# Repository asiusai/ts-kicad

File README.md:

# ts-kicad

TypeScript schematics, BOMs and KiCad settings. Requires Bun and KiCad 10 with its symbol, footprint and 3D model libraries. JLC imports also need `uv`; fabrication exports need `zip`.

1. Use builtins from `ts-kicad/lib/symbols/*` and `ts-kicad/lib/footprints/*`, or import parts with `ts-kicad jlc C123 C456`. JLC imports go into `lib/<part-number>/`, with unspecified pins made passive. For manually imported assets in `lib/<name>/`, run `ts-kicad convert [name ...]` to generate `symbols.ts` and `footprints.ts` per folder.
2. Define the circuit in `src/index.ts` and default-export a `Project`. Set footprints and manufacturer/part details in `Project.bom`. See [harness-box](examples/harness-box/src/index.ts).
3. Run `ts-kicad sync` to generate the schematic and project settings. Open KiCad, update the PCB from the schematic, then place and route the board there.
4. Run `ts-kicad export` to write BOM, PDF, fabrication files, positions and mechanical models into `outputs/`. ERC/DRC findings and schematic/PCB mismatches are logged without blocking export; JSON check reports are temporary and are not exported.

Generated labels for unnamed nets use component and pin names, such as
`Net-(Q2-G)` or `Net-(R10-Pad2)`. Explicit signal and power names remain unchanged.

Sync verifies the generated schematic through KiCad's native netlist and compares
any existing PCB's saved pad nets and full schematic UUID paths with that netlist.
Board-only footprints do not need schematic links. If these checks pass, native KiCad
schematic parity also checks symbol fields, footprint identities and escaped net
names. It reports mismatches without changing PCB placement or routing.
After an external sync, reload the schematic in KiCad before using Update PCB
from Schematic (F8); an already-open editor may still hold the previous circuit.
Project settings edited in KiCad are preserved unless explicitly set in the
TypeScript project.

Fabrication export includes KiCad's via filling/capping/plugging/covering Gerber
artwork alongside the Excellon drills. Specify the fill material in fabrication
notes and select the corresponding factory process when ordering.
Project-local fabrication notes are not copied into the outputs or Gerber ZIP.

BOM rows with an assigned JLC/LCSC part number are grouped by that number and
population status. Different schematic value labels or footprint aliases for
the same purchased part are listed together in one row. Native DNP parts are
excluded from BOM.csv and pos.csv. Their schematic and PCB flags remain intact.
Paste exports omit DNP and BOM-excluded parts. Native copper, mask, and footprint geometry remain unchanged.
Off-board variants remain separate. Parts without a supplier number group by
their full exported fields.

The JLC `pos.csv` uses millimetres and component-side rotation angles: top
angles stay unchanged; bottom angles become `180 - KiCad angle`, normalized to
0 through 360 degrees (exclusive). Coordinates are not mirrored for the bottom.
This follows [Fabrication Toolkit's conversion](https://github.com/bennymeg/Fabrication-Toolkit/blob/master/plugins/process.py).
Individual footprint zero angles can still differ from JLC's component library.
Check pin 1, polarity and connector direction in the assembly preview; matching
the native KiCad angles alone does not verify assembly orientation.

Sync keeps KiCad's complete Default netclass, including its schematic wire and
bus widths. Partial PCB netclass settings inherit these defaults. Junction dots
are calculated after power-label wires are added, so branch connections survive
the schematic editor's wire cleanup as well as command-line netlist export.

Components accept a reference first: `r("R27", { value: "100R" })` or
`new R("R27", { value: "100R" })`. Options are optional, so `new PWR_FLAG("#FLG01")`
also works. The object-only form `r({ ref: "R27", value: "100R" })` remains supported.
When both arguments specify a reference, the first argument takes precedence.

Run commands from the project directory. Separate part numbers or folder names with spaces; quote names containing spaces. The two `internal-*` commands regenerate this package's builtins during development.

```text
$ ts-kicad
Usage: ts-kicad <command> [options]

  sync                Sync the TypeScript circuit/settings into KiCad.
  export              Log ERC/DRC findings and export BOM, PDF, fabrication files, positions and mechanical models.
  convert             Generate symbols.ts and footprints.ts for all lib folders or selected folders.
  jlc                 Import JLCPCB parts into lib/PART_NO and convert those folders.
  internal-symbols    Regenerate lib/symbols from installed KiCad libraries (package development).
  internal-footprints Regenerate lib/footprints from installed KiCad libraries (package development).

Use ts-kicad <command> --help for arguments. Paths are relative to the current directory.
```

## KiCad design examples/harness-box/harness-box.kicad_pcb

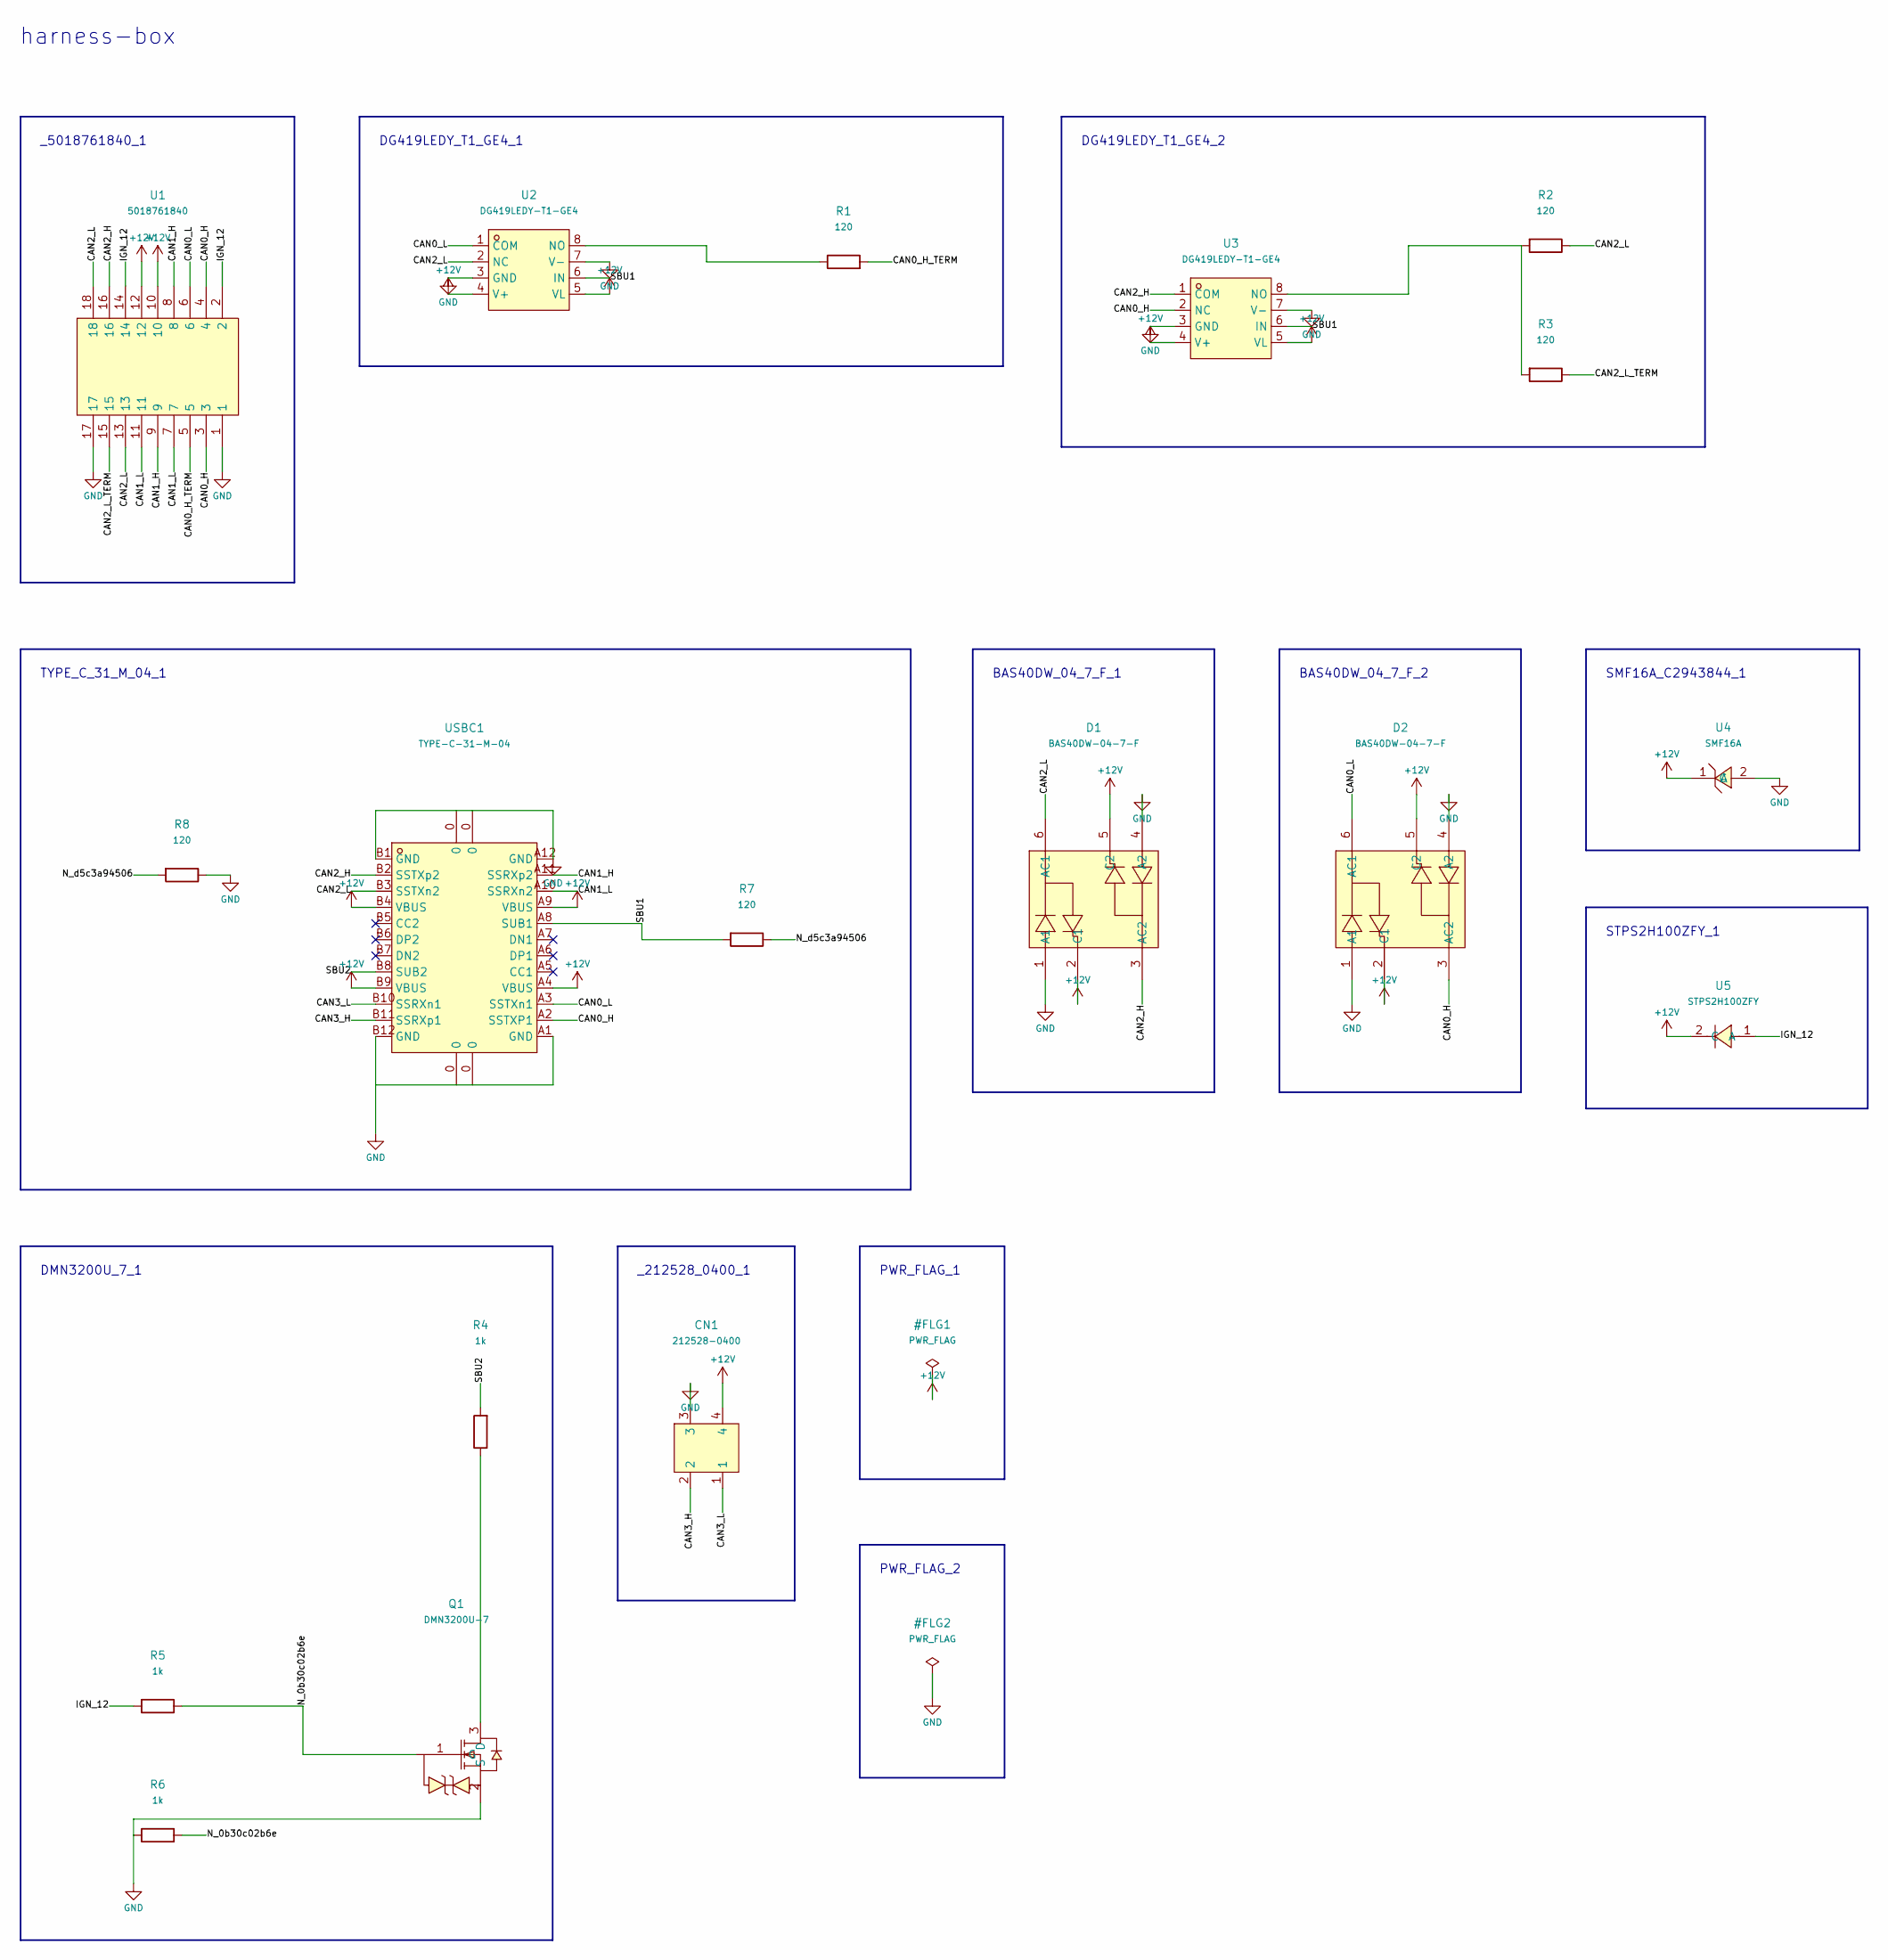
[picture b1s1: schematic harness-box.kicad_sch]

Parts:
CN1: 212528-0400; CONN-TH_4P-P3.00_212528-0400; MFR.Part # 212528-0400; JLCPCB Part # C5354889
D1, D2: BAS40DW-04-7-F; SOT-363_L2.0-W1.3-P0.65-LS2.1-BR; MFR.Part # BAS40DW-04-7-F; JLCPCB Part # C134364
Q1: DMN3200U-7; SOT-23-3_L2.9-W1.3-P1.90-LS2.4-BR; MFR.Part # DMN3200U-7; JLCPCB Part # C461018
R1, R2, R3, R7, R8: 120; R_0603_1608Metric; MFR.Part # 0603WAF1200T5E; JLCPCB Part # C22787
R4, R5, R6: 1k; R_0603_1608Metric; MFR.Part # 0603WAF1001T5E; JLCPCB Part # C21190
U1: 5018761840; CONN-TH_5018761840; MFR.Part # 5018761840; JLCPCB Part # C293583
U2, U3: DG419LEDY-T1-GE4; SO-8_L4.9-W3.9-P1.27-LS6.0-BL; MFR.Part # DG419LEDY-T1-GE4; JLCPCB Part # C2673265
U4: SMF16A; SOD-123FL_L2.7-W1.8-LS3.7-RD; MFR.Part # SMF16A; JLCPCB Part # C2943844
U5: STPS2H100ZFY; SOD-123FL_L2.6-W1.6-LS3.5-FD; MFR.Part # STPS2H100ZFY; JLCPCB Part # C2969868
USBC1: TYPE-C-31-M-04; USB-C-SMD_TYPE-C-USB-20; MFR.Part # TYPE-C-31-M-04; JLCPCB Part # C129018

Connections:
+12V: CN1.4, D1.2 (C1), D1.5 (C2), D2.2 (C1), D2.5 (C2), U1.10, U1.12, U2.4 (V+), U2.5 (VL), U3.4 (V+), U3.5 (VL), U4.1 (C), U5.2 (C), USBC1.A4 (VBUS), USBC1.A9 (VBUS), USBC1.B4 (VBUS), USBC1.B9 (VBUS)
/CAN0_H: D2.3 (AC2), U1.3, U1.4, U3.2 (NC), USBC1.A2 (SSTXP1)
/CAN0_H_TERM: R1.2, U1.5
/CAN0_L: D2.6 (AC1), U1.6, U2.1 (COM), USBC1.A3 (SSTXn1)
/CAN1_H: U1.8, U1.9, USBC1.A11 (SSRXp2)
/CAN1_L: U1.7, U1.11, USBC1.A10 (SSRXn2)
/CAN2_H: D1.3 (AC2), U1.16, U3.1 (COM), USBC1.B2 (SSTXp2)
/CAN2_L: D1.6 (AC1), R2.1, U1.13, U1.18, U2.2 (NC), USBC1.B3 (SSTXn2)
/CAN2_L_TERM: R3.1, U1.15
/CAN3_H: CN1.2, USBC1.B11 (SSRXp1)
/CAN3_L: CN1.1, USBC1.B10 (SSRXn1)
/IGN_12: R5.2, U1.2, U1.14, U5.1 (A)
/N_0b30c02b6e: Q1.1 (G), R5.1, R6.2
/N_d5c3a94506: R7.1, R8.2
/SBU1: R7.2, U2.6 (IN), U3.6 (IN), USBC1.A8 (SUB1)
/SBU2: R4.2, USBC1.B8 (SUB2)
GND: CN1.3, D1.1 (A1), D1.4 (A2), D2.1 (A1), D2.4 (A2), Q1.2 (S), R6.1, R8.1, U1.1, U1.17, U2.3 (GND), U2.7 (V-), U3.3 (GND), U3.7 (V-), U4.2 (A), USBC1.0, USBC1.A1 (GND), USBC1.A12 (GND), USBC1.B1 (GND), USBC1.B12 (GND)
unnamed: Q1.3 (D), R4.1
unnamed: R1.1, U2.8 (NO)
unnamed: R2.2, R3.2, U3.8 (NO)

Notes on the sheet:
harness-box
_5018761840_1
DG419LEDY_T1_GE4_1
DG419LEDY_T1_GE4_2
TYPE_C_31_M_04_1
BAS40DW_04_7_F_1
BAS40DW_04_7_F_2
SMF16A_C2943844_1
STPS2H100ZFY_1
DMN3200U_7_1
_212528_0400_1
PWR_FLAG_1
PWR_FLAG_2

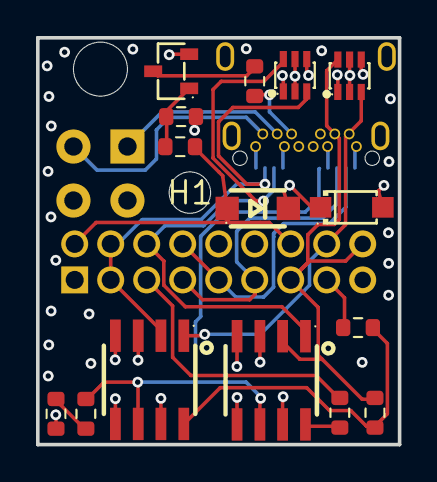
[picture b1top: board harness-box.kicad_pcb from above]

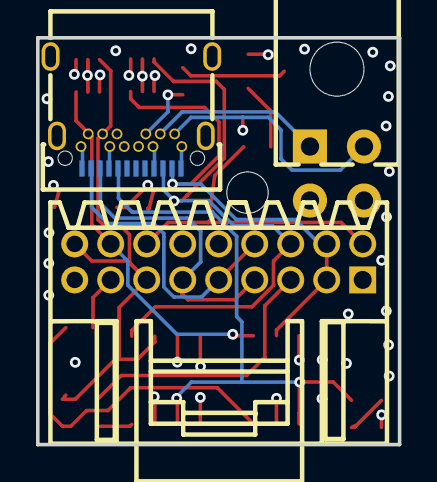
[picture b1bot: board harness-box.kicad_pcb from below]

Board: 4 copper layers, 20.1 x 22.6 mm, 19 parts (3 on the bottom side), 20 nets.

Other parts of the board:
H1: MountingHole_2.3mm
